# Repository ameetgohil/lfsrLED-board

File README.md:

# lfsrLED-board
555 timer and shift register chip use to create led light up pattern

Reference:
The board design follows Ashley Mills tutorial on youtube: https://www.youtube.com/playlist?list=PLCNJWVn9MJuORLQ3ds_U3D7RILfE4zdoL

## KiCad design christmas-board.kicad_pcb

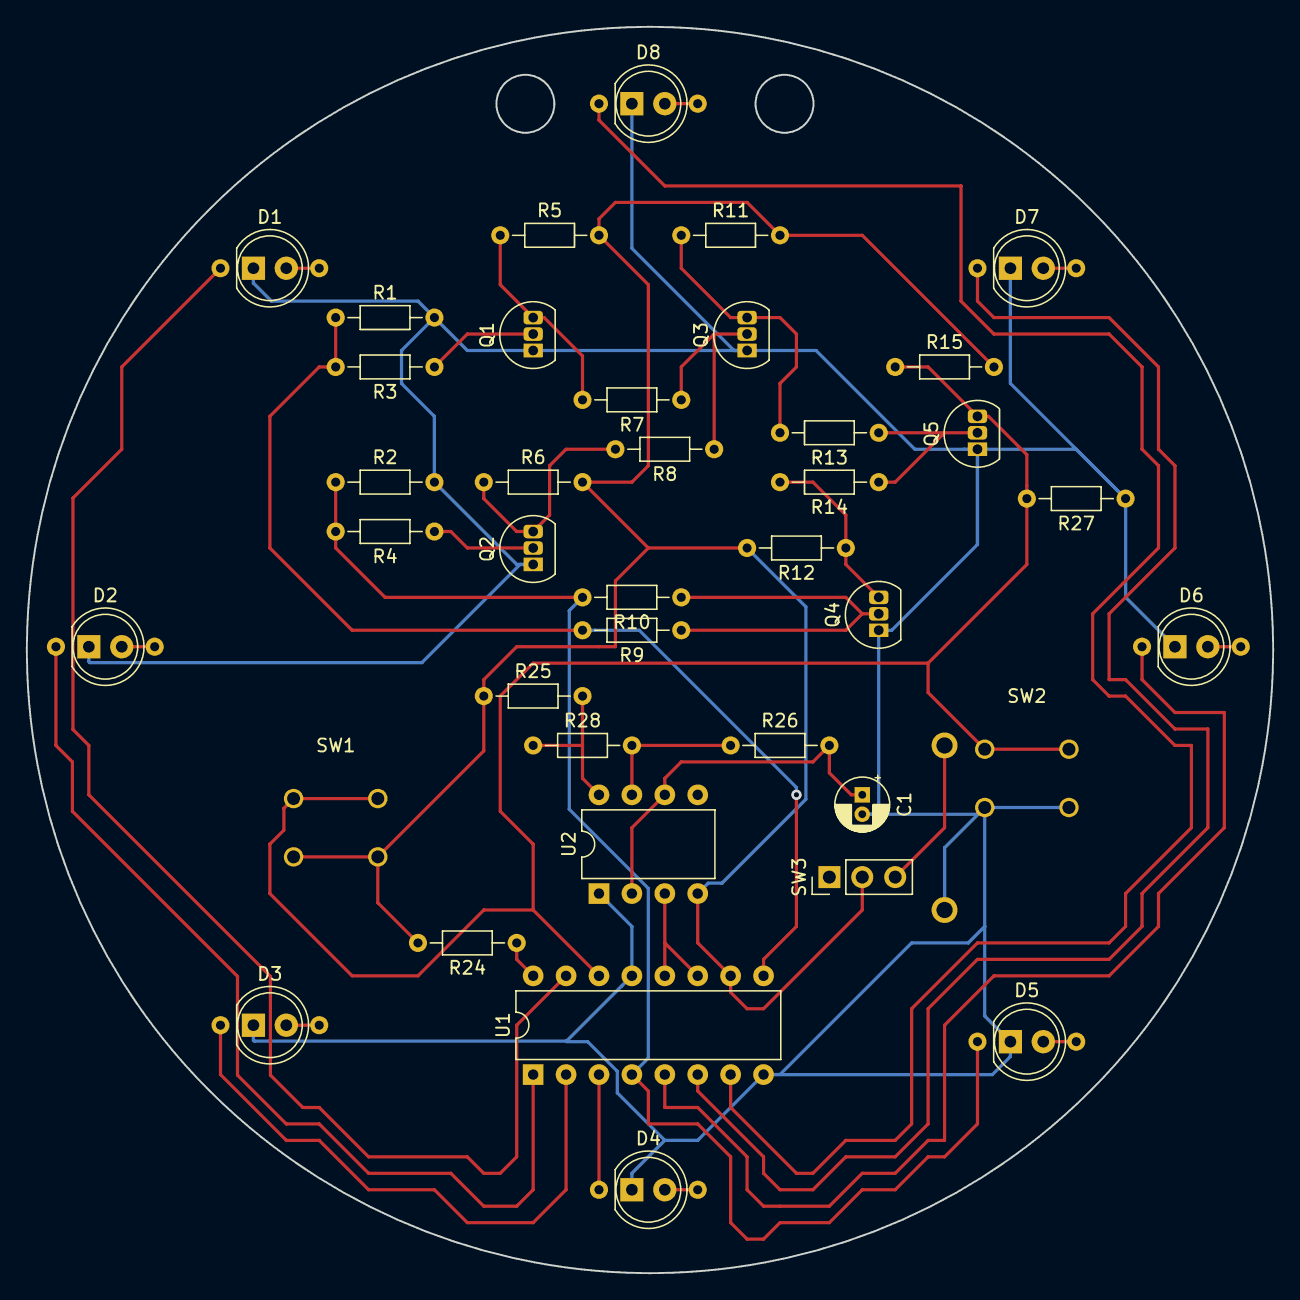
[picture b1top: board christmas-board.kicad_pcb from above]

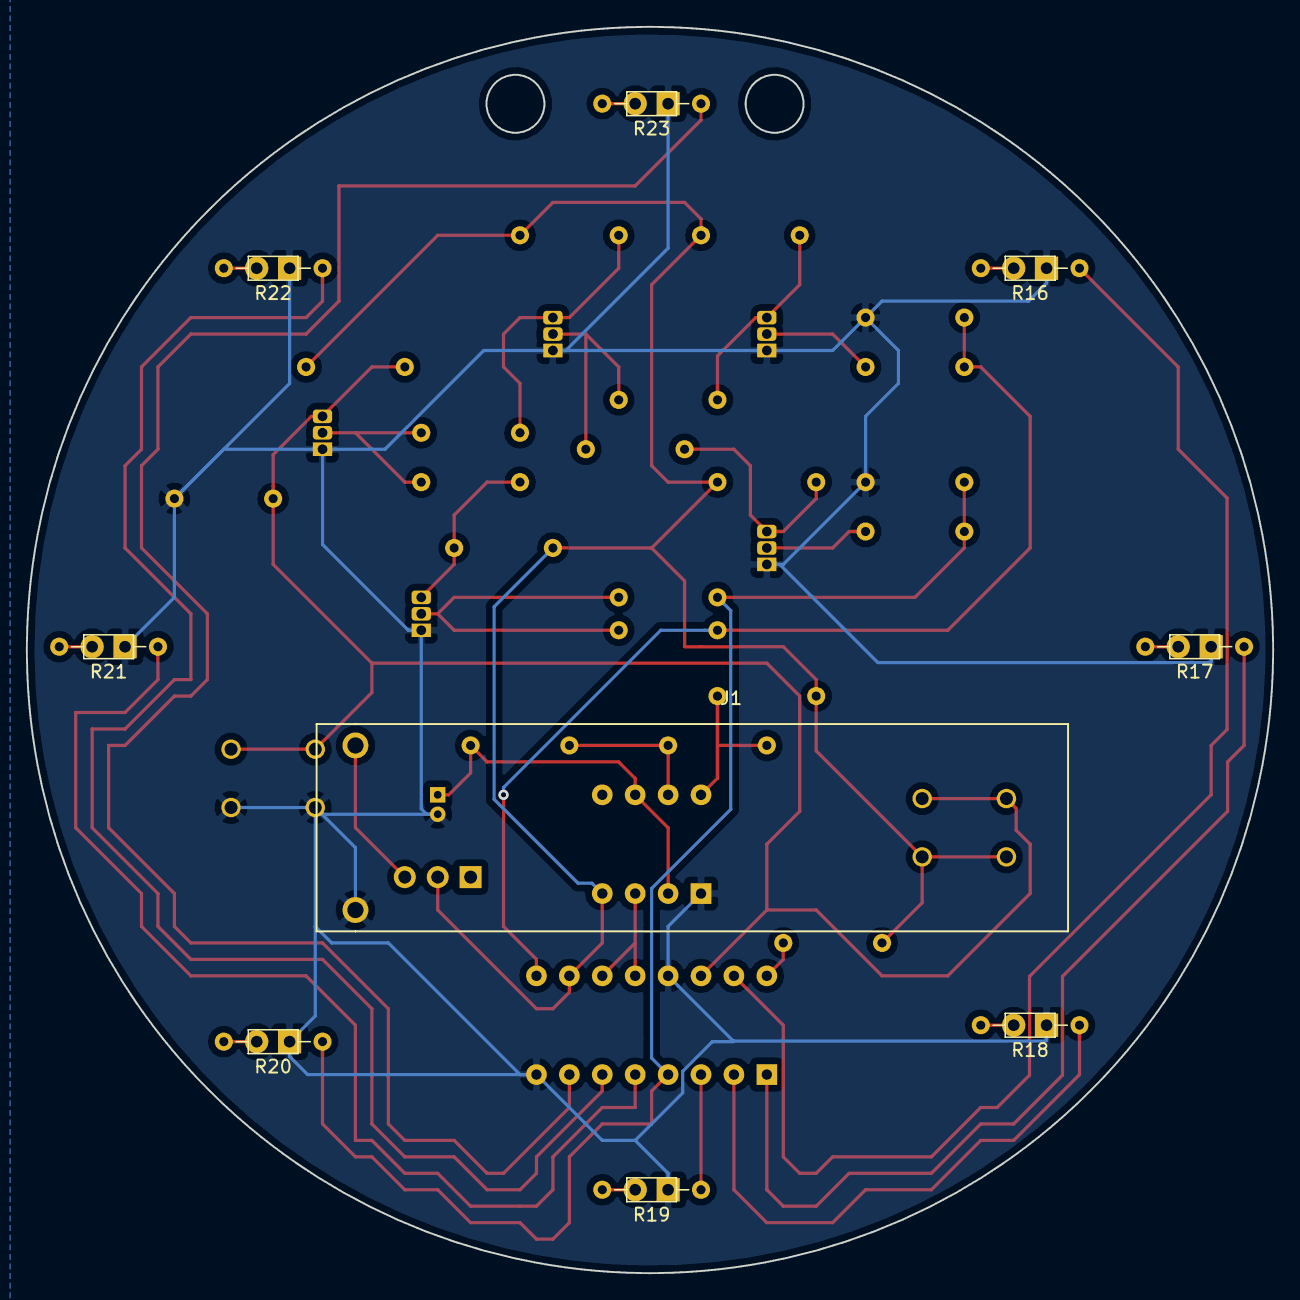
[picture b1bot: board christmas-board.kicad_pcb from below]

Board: 2 copper layers, 96.2 x 96.2 mm, 48 parts (9 on the bottom side), 35 nets.

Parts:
C1: 22uF; CP_Radial_D4.0mm_P1.50mm
D1, D2, D3, D4, D5, D6, D7, D8: LED; LED_D5.0mm
J1: Conn_01x02_Female; battery_holder_2468
Q1, Q2, Q3, Q4, Q5: Q_NPN_EBC; TO-92L_Inline
R1, R2, R3, R4, R26, R27: 10k; R_Axial_DIN0204_L3.6mm_D1.6mm_P7.62mm_Horizontal
R5, R6, R11, R12, R15: 4.7K; R_Axial_DIN0204_L3.6mm_D1.6mm_P7.62mm_Horizontal
R7, R8, R9, R10, R13, R14, R28: 10K; R_Axial_DIN0204_L3.6mm_D1.6mm_P7.62mm_Horizontal
R16, R17, R18, R19, R20, R21, R22, R23: R; R_Axial_DIN0204_L3.6mm_D1.6mm_P7.62mm_Horizontal
R24, R25: 470; R_Axial_DIN0204_L3.6mm_D1.6mm_P7.62mm_Horizontal
SW1, SW2: SW_Push; Tactile_Shallow_SW
SW3: SW_SPDT; PinHeader_1x03_P2.54mm_Vertical
U1: 595_SHIFT; DIP-16_W7.62mm
U2: 555; DIP-8_W7.62mm

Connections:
/555_OUT: U1.11, U1.12, U2.3
/LED_A: R16.1, U1.15
/LED_B: R17.1, U1.1
/LED_C: R18.1, U1.2
/LED_D: R19.1, U1.3
/LED_E: R2.1, R4.2, R10.2, R20.1, U1.4
/LED_F: R21.1, U1.5
/LED_G: R22.1, U1.6
/LED_H: R23.1, U1.7
/PULL_HIGH: Q5.3, R15.1, R27.2, SW1.2, SW2.2, U1.14
/XOR_IN_A: R1.1, R3.2, R9.2, U1.9
GND: C1.2, D1.1, D2.1, D3.1, D4.1, D5.1, D6.1, D7.1, D8.1, J1.2, Q1.1, Q2.1, Q3.1, Q4.1, Q5.1, R1.2, R2.2, R27.1, SW2.1, U1.8, U1.13, U2.1
unnamed: C1.1, R26.2, U2.2, U2.6
unnamed: D1.2, R16.2
unnamed: D2.2, R17.2
unnamed: D3.2, R18.2
unnamed: D4.2, R19.2
unnamed: D5.2, R20.2
unnamed: D6.2, R21.2
unnamed: D7.2, R22.2
unnamed: D8.2, R23.2
unnamed: J1.1, SW3.3
unnamed: Q1.2, R3.1
unnamed: Q1.3, R5.1, R7.2
unnamed: Q2.2, R4.1
unnamed: Q2.3, R6.1, R8.2
unnamed: Q3.2, R7.1, R8.1
unnamed: Q3.3, R11.1, R13.2
unnamed: Q4.2, R9.1, R10.1
unnamed: Q4.3, R12.1, R14.2
unnamed: Q5.2, R13.1, R14.1
unnamed: R24.1, U1.16
unnamed: R25.2, R28.1, U2.8
unnamed: R26.1, R28.2, U2.7
VCC: R5.2, R6.2, R11.2, R12.2, R15.2, R24.2, R25.1, SW1.1, SW3.2, U1.10, U2.4

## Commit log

2018-09-21 initial schematic capture complete
2018-09-21 assigned footprints to components
2018-09-22 parital part placement
2018-09-23 LED routing complete
2018-09-23 fix footprint on npn - swich to EBC ro CBE
2018-09-25 signal tracks complete
2018-09-25 sw footprint added
2018-09-25 initial routing complete
2018-09-26 switch added, tracks updated
2018-09-26 add battery holder
2018-09-26 gerbers generated
